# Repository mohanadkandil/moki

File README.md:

<div align="center">
  
  <h1>Moki</h1>
  <p>A little workshop for your next invention.</p>
  <p>
    <a href="#how-it-works">How it works</a> &nbsp;·&nbsp;
    <a href="#architecture">Architecture</a> &nbsp;·&nbsp;
    <a href="#run-locally">Run locally</a>
  </p>
</div>

Moki turns a description of a device into a schematic, a routed PCB, a printable case and compiled firmware. Code checks each of those files. Nothing Moki designed has been fabricated or powered yet, so a finished build is a checked design, not a proven device.

## How it works

1. **Describe the device.** The Verifier turns your words into requirements code can check and asks about anything vague. It also picks the route: a carrier board for kit modules, a chip-level board from real LCSC parts, or a board with no microcontroller.
2. **Confirm the requirements.** The Designer writes a plan: structured data listing kit modules or blocks, which are reusable chip-level circuits. If the library lacks a block, the Block Author finds a real part, reads its datasheet and writes one.
3. **The plan goes through gates.** Code runs ERC, the requirement checks and SPICE. On chip-level boards, a separate Reviewer checks the schematic against datasheets, and code confirms each quote appears on the cited page. The Firmware agent's code has to compile.
4. **Moki builds it.** The plan becomes a routed board, a case and a firmware project, and DRC runs on the result. When a gate fails, the Fixer gets at most 2 tries. After that the build stops and the chat names the gate.
5. **Inspect and change it.** Each project opens at `/studio/<id>`, with Schematic, PCB, 3D, Case and Firmware tabs. Edit on the canvas or in the chat. Either way the plan changes, the gates run again and the files are rebuilt. Download the Gerbers, BOM, pick-and-place, KiCad project, STEP, STL and firmware.

## Architecture

Models decide; code builds and checks. The agents share one plan instead of talking to each other, and the PCB, case and firmware are all regenerated from it. Code owns everything measurable, including board size, placement legality, prices and the gates, and each turn has a $2 budget cap. Every model call crosses one seam, `src/agents/model.ts`. OpenAI `gpt-6.1-sol` is the provider in use, and an Anthropic adapter and a replay adapter for tests sit at the same seam.

Agents build through the same job interface the studio uses, so a model can't do anything a maker's browser couldn't. One queue owns every build: one at a time, with up to 5 waiting. Workers are subprocesses with timeouts and an environment allowlist, which keeps model keys away from them, but this isn't a sandbox: generated board code runs on the host. Only model-written firmware compiles in a sandbox with no network, and it is never run.

[SVG](docs/diagrams/moki-architecture.svg) · [How the diagram is built, and the code behind each node](docs/diagrams/README.md)

| Part | Tools |
| --- | --- |
| Web | React 19, Vite 8, Three.js, Manrope |
| Server | Node 22, TypeScript, Vite-plugin APIs, SSE |
| Agents | OpenAI SDK, `gpt-6.1-sol` |
| Electronics | tscircuit 0.0.3075 in Bun 1.4: schematic, PCB, autorouting, Gerbers, BOM, GLB, KiCad export |
| Case | build123d 0.13 on Python 3.12: STEP and STL |
| Firmware | PlatformIO 6.1, compiled under bubblewrap |
| Simulation | ngspice, through `@tscircuit/ngspice-spice-engine` |
| Parts | JLCPCB and LCSC catalog via jlcsearch, EasyEDA importer |
| Datasheets | pdf.js, with citations checked by code; Nemotron 3.5 Parse on Modal for tables and layout |
| Saved work | JSON and generated files under `var/`, with no database |

## What works

**Kit boards build in about half a minute.** Each template ran 5 times cold and 3 times with its EDA cache, on an 8-core arm64 server with 16 GB. Every run produced a routed 2-layer board with 0 DRC errors, a case and compiled firmware.

| Template | Cold p50 | Cold p95 | Cached p50 |
| --- | --- | --- | --- |
| focus-timer | 31.2 s | 32.2 s | 19.0 s |
| light-lamp | 25.8 s | 27.4 s | 12.5 s |
| temp-monitor | 31.7 s | 34.0 s | 19.1 s |

**Agents handled all 11 briefs in the live kit bench as expected.** With `gpt-6.1-sol`, 6 built with 0 DRC errors and compiled firmware, and 5 were correctly declined as out of scope. The whole bench cost $0.103. A successful build cost $0.010 to $0.016 and took 9.8 to 12.2 s of agent time.

**Chip-level boards build when the plan is replayed.** Replays script the model calls and run everything else for real. A night light (20 × 42 mm) and a water-leak buzzer (28 × 56 mm) built with no firmware stage, and no-MCU boards take about 15 s. One exact RP2040 plan from a live run passes every gate, with 0 DRC errors and compiled firmware.

**Tests.** `npm test` runs about 1,320 tests, most of them added after a real failure.

## What isn't proven

- **No hardware.** Nothing has been fabricated, flashed or powered. Every check is a software check.
- **No live chip-level build.** 12 live runs cost $6.00 in total. A run that reached review cost $0.50 to $0.90 and took 4 to 11 minutes, and none has yet built a board end to end.
- **Dense routing.** This is the weak spot. An RP2040 with a DRV8833 takes 160 to 389 s, and some plans fail DRC or hit the 10-minute timeout.
- **Isolation.** Generated board code runs on the host, so per-build micro-VMs are needed before more than one person uses it.
- **Reviewed blocks.** A new block stays labelled unreviewed until an independent review promotes it.
- **Datasheet tables.** pdf.js flattens tables and can't see figures. Nemotron 3.5 Parse on Modal reads them for the agents. On 5 datasheets it read 81 of 81 pin-table rows and 48 of 50 electrical values, at about 6.7 s per page on an L4 GPU. In that first test it didn't beat a pdfplumber baseline on tables, and its clear gain was text on image-only pages.

## Run locally

You need Node 22 or newer, [Bun](https://bun.sh), Python 3.12 with `venv`, and an OpenAI API key. Firmware also needs [PlatformIO](https://platformio.org) with `pio` on your `PATH`.

```sh
npm ci
(cd eda && bun install --frozen-lockfile)
python3 -m venv ~/.local/share/moki-tools/build123d-venv
~/.local/share/moki-tools/build123d-venv/bin/pip install -r mech/requirements.txt
cp .env.example .env   # then set OPENAI_API_KEY
npm run dev
```

Open http://127.0.0.1:5173/. Without a key the app still opens, with the agents off.

Compiling model-written firmware also needs `bwrap`, and `src/agents/pio-sandbox.sh` has its tool folder fixed in `TOOLS` on line 6, so change that for your machine.

| Variable | What it does |
| --- | --- |
| `OPENAI_API_KEY` | Turns the agents on. Keep it on the server. |
| `OPENAI_MODEL` | Defaults to `gpt-6.1-sol`. |
| `MOKI_AGENT_PROVIDER` | Set to `openai` if an Anthropic key is also in your environment. That key wins otherwise. |
| `MOKI_AGENTS=off`, `MOKI_CHIP=off` | Turn off the agents, or just chip-level boards. |
| `MOKI_BUN`, `MOKI_BUILD123D_PYTHON`, `MOKI_PLATFORMIO` | Point at tools installed somewhere else. |
| `MOKI_PARSE_URL`, `MOKI_PARSE_TOKEN` | Connect the Nemotron parse service. Without them, agents read pdf.js text. |
| `MOKI_CHIP_TIMEOUT_MS` | Chip-level build limit, 10 minutes by default. |
| `MOKI_PROJECTS_DIR`, `MOKI_BOARD_JOBS_DIR` | Move saved projects and build jobs out of `var/`. |
| `MOKI_BASE_PATH`, `MOKI_PUBLIC_HOST`, `MOKI_BOARD_API_TOKEN` | For hosting. On a public host with no token, the agents stay off. |

Check your work with:

```sh
npm run typecheck
npm test
npm run build
```

`npm run preview` serves that build at http://127.0.0.1:8847/app/moki/.

Code from the earlier computer-use prototype is still in `server/workshop-api.ts`, `server/desktop-api.ts` and `scripts/`. Its routes exist only under `npm run dev`, and ADR 0001 explains why it was replaced.

## Decisions

- [ADR 0001: Code-first EDA instead of computer-use GUI agents](docs/adr/0001-code-first-eda-over-computer-use.md)
- [ADR 0002: Agent pipeline where models decide and code builds and checks](docs/adr/0002-agent-pipeline-models-decide-code-checks.md)
- [ADR 0003: Layout-aware datasheet parsing with Nemotron 3.5 Parse on Modal](docs/adr/0003-datasheet-layout-parsing-nemotron-parse.md) (accepted)

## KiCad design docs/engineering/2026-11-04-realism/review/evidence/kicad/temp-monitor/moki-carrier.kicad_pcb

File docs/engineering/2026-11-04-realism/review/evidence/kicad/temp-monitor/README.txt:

Open moki-carrier.kicad_pro in KiCad. Converted with circuit-json-to-kicad; review design rules, net assignments and fabrication outputs before manufacturing. Module outlines and fit are catalog estimates. The detailed Moki recognition models are embedded in board.glb, not KiCad.

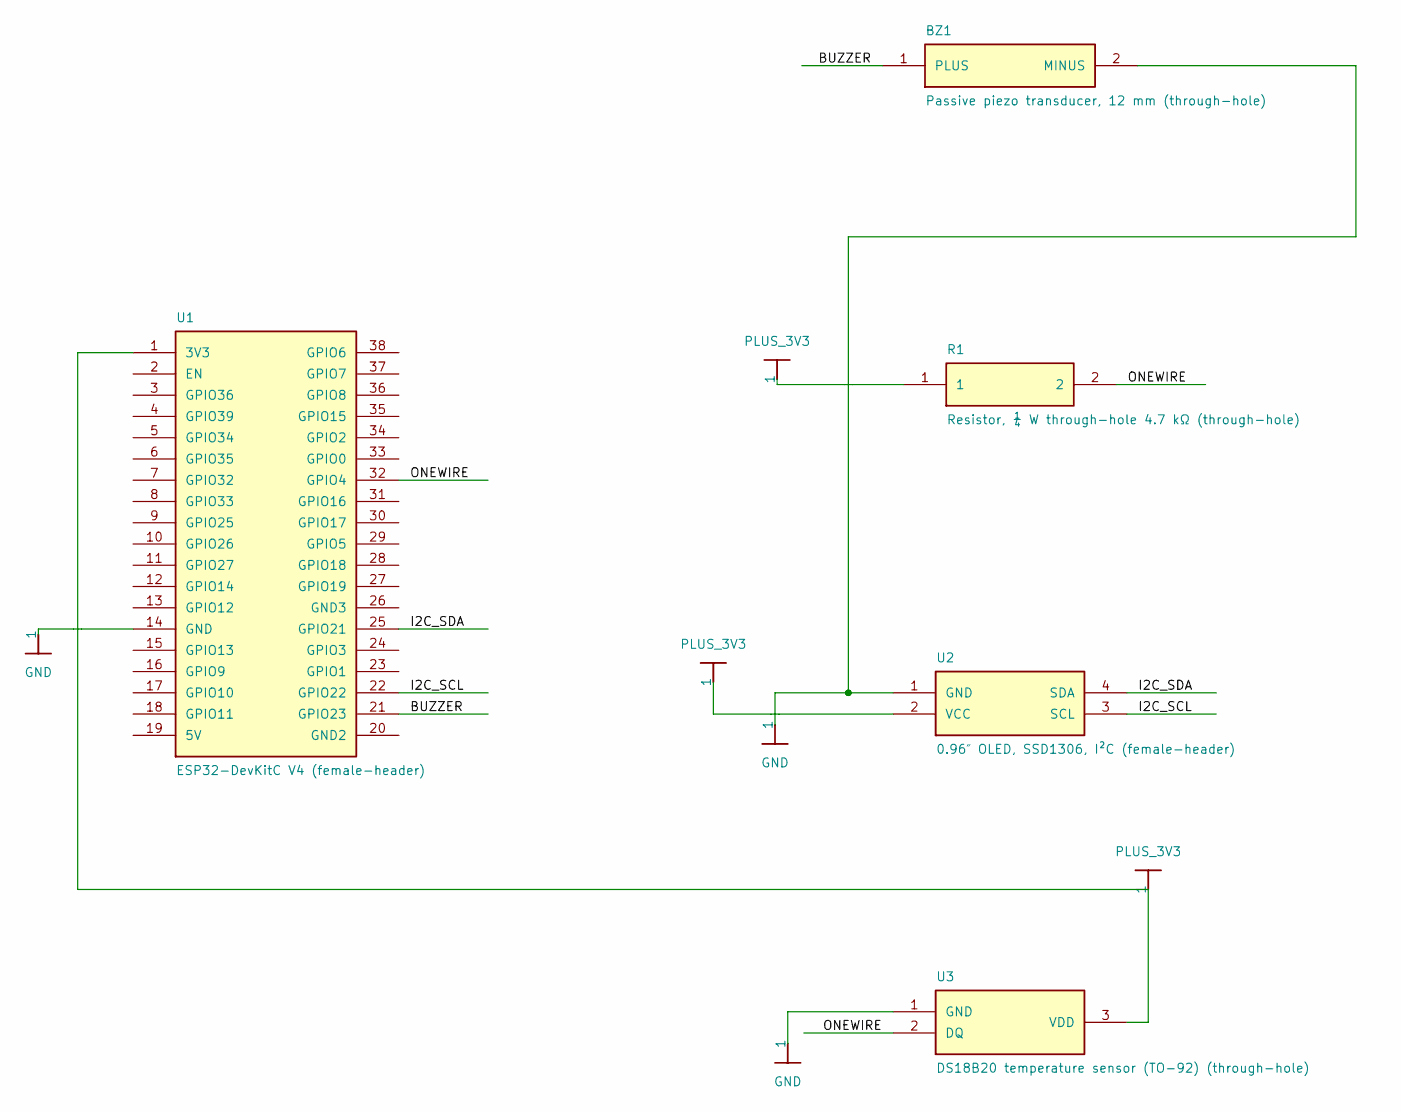
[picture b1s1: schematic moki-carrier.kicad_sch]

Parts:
BZ1: Passive piezo transducer, 12 mm (through-hole)
R1: Resistor, ¼ W through-hole 4.7 kΩ (through-hole)
U1: ESP32-DevKitC V4 (female-header)
U2: 0.96″ OLED, SSD1306, I²C (female-header)
U3: DS18B20 temperature sensor (TO-92) (through-hole)

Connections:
BUZZER: BZ1.1 (PLUS), U1.21 (GPIO23)
GND: BZ1.2 (MINUS), U1.14 (GND), U2.1 (GND), U3.1 (GND)
I2C_SCL: U1.22 (GPIO22), U2.3 (SCL)
I2C_SDA: U1.25 (GPIO21), U2.4 (SDA)
ONEWIRE: R1.2, U1.32 (GPIO4), U3.2 (DQ)
PLUS_3V3: R1.1, U1.1 (3V3), U2.2 (VCC), U3.3 (VDD)

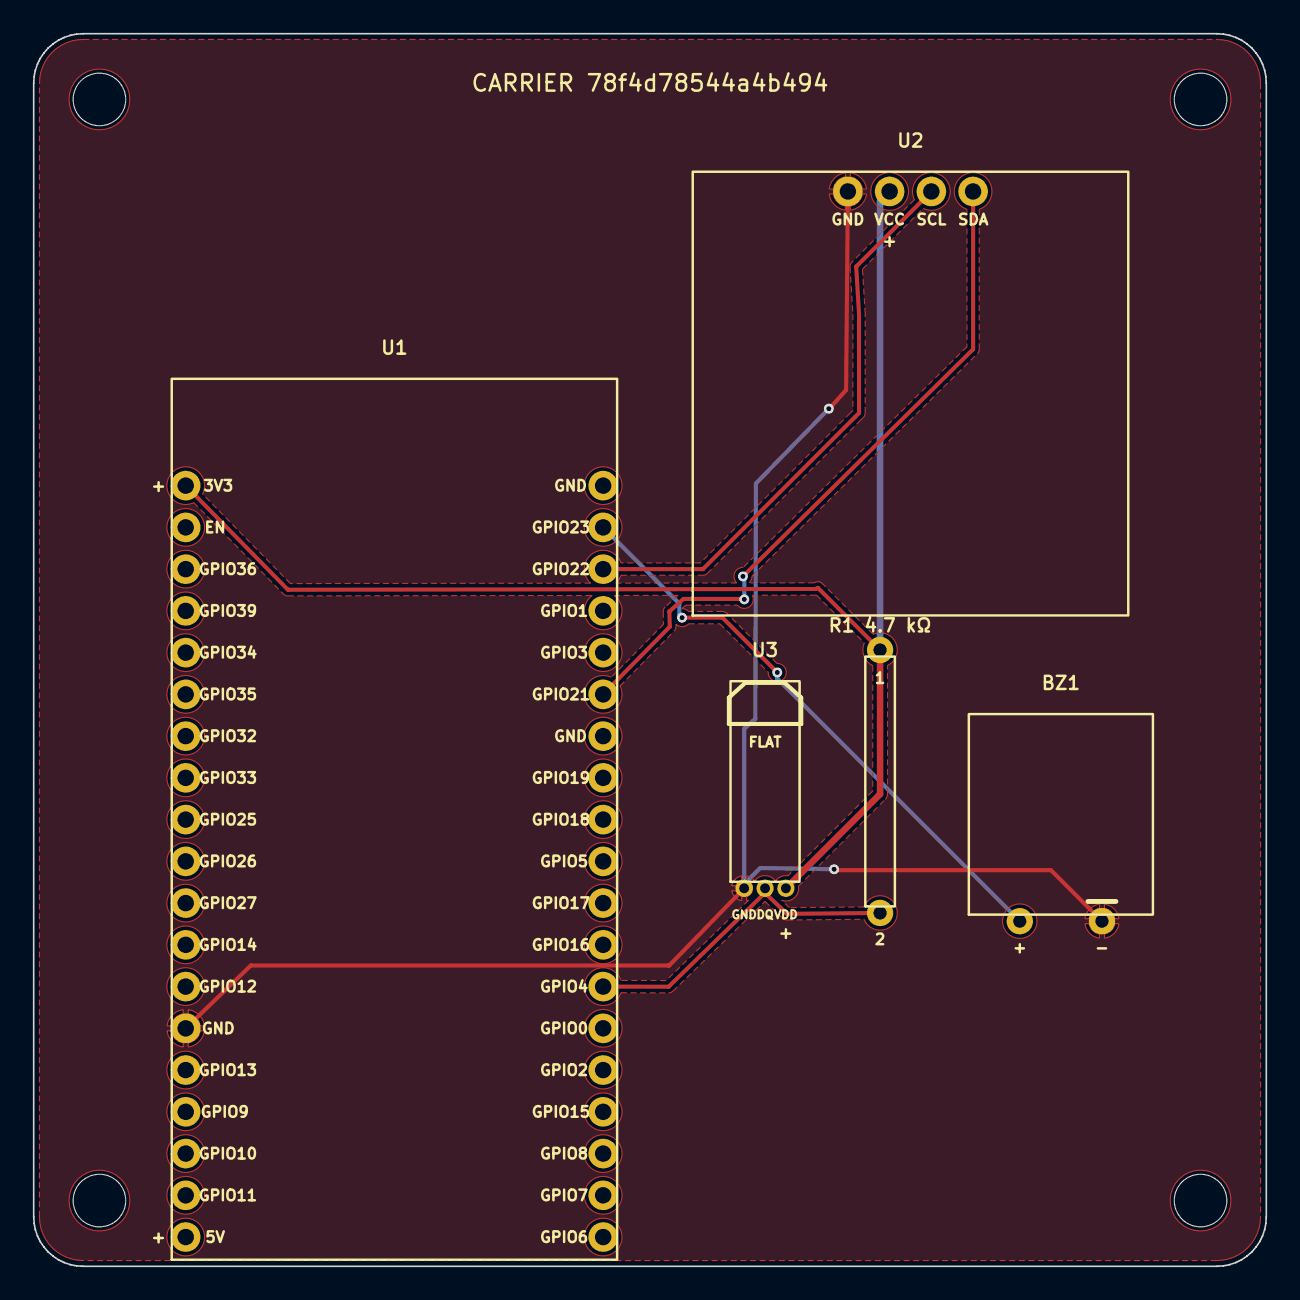
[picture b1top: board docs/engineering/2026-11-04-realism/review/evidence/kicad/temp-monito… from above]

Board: 2 copper layers, 75.0 x 75.0 mm, 5 parts (0 on the bottom side), 6 nets.

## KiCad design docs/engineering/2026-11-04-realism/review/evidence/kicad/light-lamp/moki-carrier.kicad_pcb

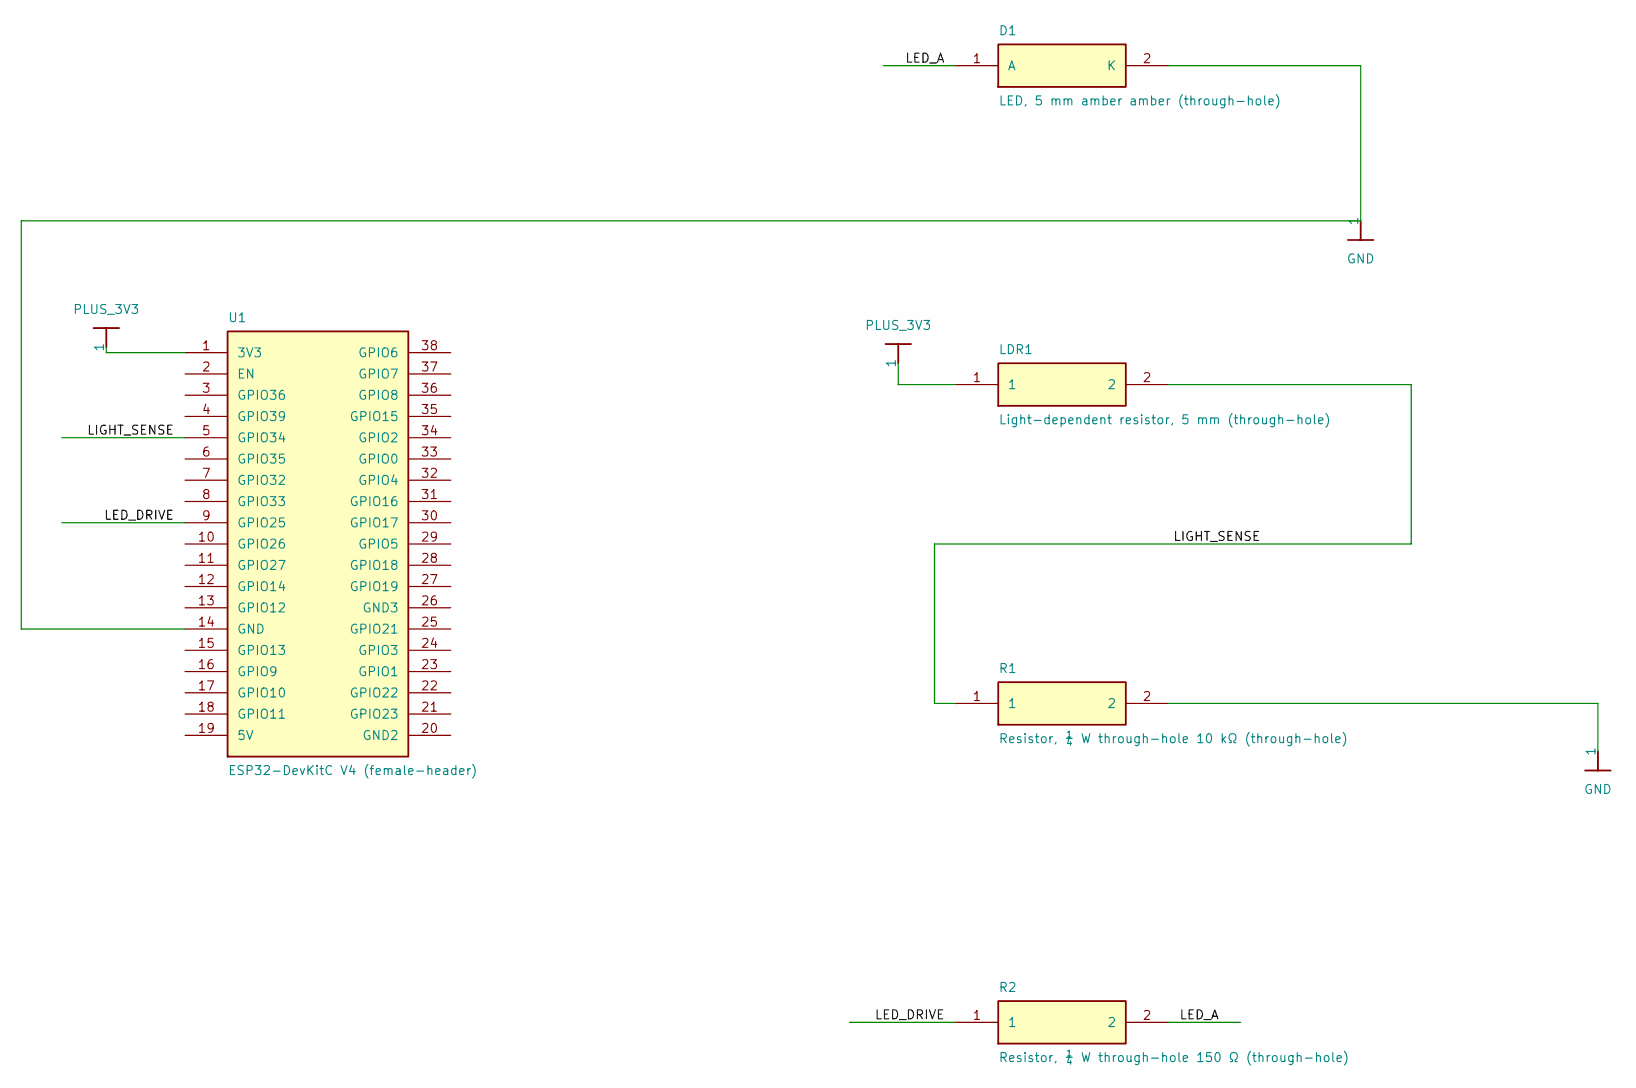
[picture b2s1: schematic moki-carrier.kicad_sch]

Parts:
D1: LED, 5 mm amber amber (through-hole)
LDR1: Light-dependent resistor, 5 mm (through-hole)
R1: Resistor, ¼ W through-hole 10 kΩ (through-hole)
R2: Resistor, ¼ W through-hole 150 Ω (through-hole)
U1: ESP32-DevKitC V4 (female-header)

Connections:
GND: D1.2 (K), R1.2, U1.14 (GND)
LED_A: D1.1 (A), R2.2
LED_DRIVE: R2.1, U1.9 (GPIO25)
LIGHT_SENSE: LDR1.2, R1.1, U1.5 (GPIO34)
PLUS_3V3: LDR1.1, U1.1 (3V3)

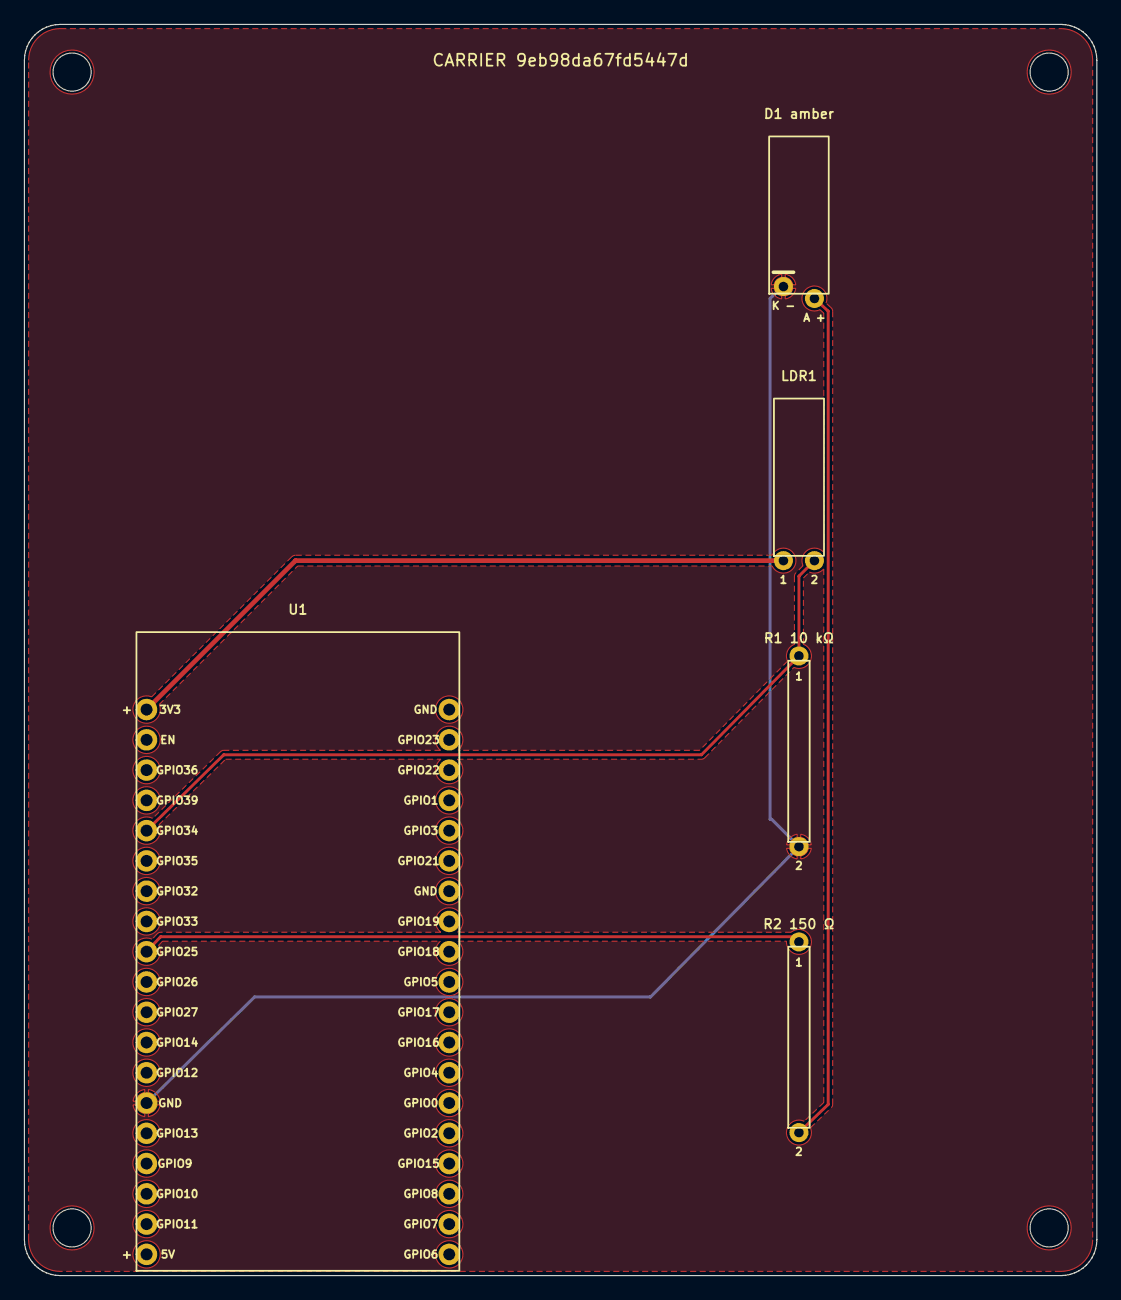
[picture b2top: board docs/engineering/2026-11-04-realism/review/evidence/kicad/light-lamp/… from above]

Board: 2 copper layers, 90.0 x 105.0 mm, 5 parts (0 on the bottom side), 5 nets.

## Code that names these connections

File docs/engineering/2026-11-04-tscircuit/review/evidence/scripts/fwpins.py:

import json,re,sys,zipfile
cat=json.load(open(sys.argv[1]))
for job in sys.argv[2:]:
    d=json.load(open(f'{job}/design.json')); z=zipfile.ZipFile(f'{job}/firmware.zip')
    names=z.namelist(); pinsn=[n for n in names if n.endswith('pins.h')][0]
    pins={m.group(1):int(m.group(2)) for m in re.finditer(r'PIN_(\w+) = (\d+)',z.read(pinsn).decode())}
    parts={p['id']:p for p in d['parts']}
    bymod={p['module']:p['id'] for p in d['parts']}
    nets={}
    for n in d['nets']:
        for e in n['endpoints']: nets[(e['part'],e['pin'])]=n
    def gpio_of(net):
        g=[e['pin'] for e in net['endpoints'] if e['part']=='U1' and e['pin'].startswith('GPIO')]
        assert len(g)==1,net; return int(g[0][4:])
    expected={}
    t=d['template']
    if 'ssd1306-oled-128x64-i2c' in bymod or 'bme280-i2c-4pin' in bymod:
        bus=bymod.get('ssd1306-oled-128x64-i2c') or bymod['bme280-i2c-4pin']
        expected['I2C_SDA']=gpio_of(nets[(bus,'SDA')]);expected['I2C_SCL']=gpio_of(nets[(bus,'SCL')])
    if 'piezo-passive-12mm' in bymod: expected['BUZZER']=gpio_of(nets[(bymod['piezo-passive-12mm'],'+')])
    if t=='focus-timer':
        s=bymod['ky040-rotary-encoder']; expected.update(ENCODER_A=gpio_of(nets[(s,'CLK')]),ENCODER_B=gpio_of(nets[(s,'DT')]),ENCODER_SW=gpio_of(nets[(s,'SW')]))
    if t=='light-lamp':
        expected['LIGHT_SENSE']=gpio_of(nets[('LDR1','2')])
        # D1.A -> R2 -> other side
        an=nets[('D1','A')]; r=[e for e in an['endpoints'] if e['part']!='D1'][0]
        other='2' if r['pin']=='1' else '1'; expected['LED']=gpio_of(nets[(r['part'],other)])
    if 'ds18b20-to92' in bymod: expected['ONEWIRE']=gpio_of(nets[(bymod['ds18b20-to92'],'DQ')])
    print(t,job[-36:-28],'MATCH' if expected==pins else 'DIFF',pins,'' if expected==pins else expected)
    caps={p['id']:p for p in cat['esp32-devkitc-v4']['pins']}
    for k,v in pins.items():
        c=caps[f'GPIO{v}']['gpio']; print(f'    {k}=GPIO{v} out={c["output"]} adc1={c["adc1"]} reserved={c.get("reserved")}')
    b=json.load(z.open(pinsn) if False else open(f'{job}/firmware-build.json'))
    print('    compile',b['status'],b['flash'],b['ram'],b['physicalFlash'])
